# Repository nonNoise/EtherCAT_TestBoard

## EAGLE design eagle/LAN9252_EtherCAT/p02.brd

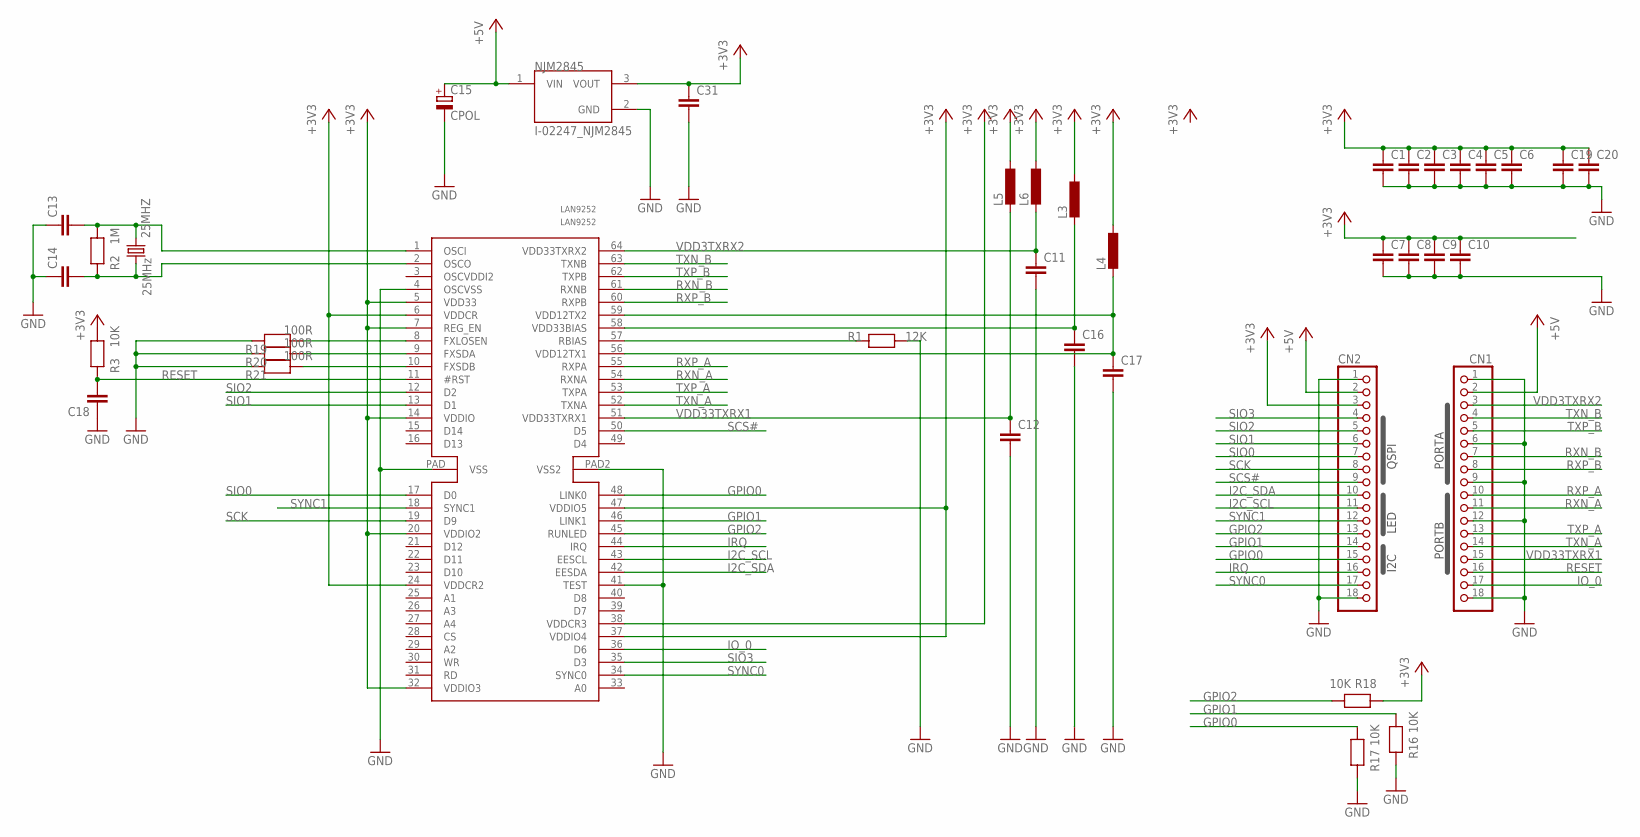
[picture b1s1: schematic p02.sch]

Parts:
25MHZ: 25MHz; HC49/S
C1, C2, C3, C4, C5, C6, C7, C8, C9, C10, C11, C12, C13, C14, C16, C17, C18, C31: C_1068; C0603
C15: CPOL; 153CLV-0605
C19, C20: C_2012; C0805K
CN1, CN2: PINHD-1X18; 1X18
L3, L4, L5, L6: L-EUL2012C; L2012C
LAN9252: LAN9252; QFN-64_02
NJM2845: I-02247_NJM2845; TO252
R1: 12K; R0603
R2: 1M; R0603
R3, R16, R17, R18: 10K; R0603
R19, R20, R21: 100R; R0603

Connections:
+3V3: C1.1, C2.1, C3.1, C4.1, C5.1, C6.1, C7.1, C8.1, C9.1, C10.1, C19.1, C20.1, C31.1, CN2.3, L3.1, L4.1, L5.1, L6.1, LAN9252.5 (VDD33), LAN9252.6 (VDDCR), LAN9252.7 (REG_EN), LAN9252.14 (VDDIO), LAN9252.20 (VDDIO2), LAN9252.24 (VDDCR2), LAN9252.32 (VDDIO3), LAN9252.37 (VDDIO4), LAN9252.38 (VDDCR3), LAN9252.47 (VDDIO5), NJM2845.3 (VOUT), R3.2, R18.1
+5V: C15.+, CN1.2, CN2.2, NJM2845.1 (VIN)
GND: C1.2, C2.2, C3.2, C4.2, C5.2, C6.2, C7.2, C8.2, C9.2, C10.2, C11.2, C12.2, C13.1, C14.1, C15.-, C16.2, C17.2, C18.1, C19.2, C20.2, C31.2, CN1.1, CN1.6, CN1.9, CN1.12, CN1.18, CN2.1, CN2.18, LAN9252.4 (OSCVSS), LAN9252.41 (TEST), LAN9252.PAD (VSS), LAN9252.PAD2 (VSS2), NJM2845.2 (GND), R1.1, R16.1, R17.1, R19.1, R20.1, R21.1
GPIO0: CN2.15, LAN9252.48 (LINK0), R17.2
GPIO1: CN2.14, LAN9252.46 (LINK1), R16.2
GPIO2: CN2.13, LAN9252.45 (RUNLED), R18.2
I2C_SCL: CN2.11, LAN9252.43 (EESCL)
I2C_SDA: CN2.10, LAN9252.42 (EESDA)
IO_0: CN1.17, LAN9252.36 (D6)
IRQ: CN2.16, LAN9252.44 (IRQ)
unnamed: LAN9252.57 (RBIAS), R1.2
unnamed: LAN9252.8 (FXLOSEN), R19.2
unnamed: LAN9252.9 (FXSDA), R20.2
unnamed: 25MHZ.2, C13.2, LAN9252.1 (OSCI), R2.2
unnamed: C17.1, L4.2, LAN9252.56 (VDD12TX1), LAN9252.59 (VDD12TX2)
unnamed: 25MHZ.1, C14.2, LAN9252.2 (OSCO), R2.1
unnamed: LAN9252.10 (FXSDB), R21.2
unnamed: C16.1, L3.2, LAN9252.58 (VDD33BIAS)
RESET: C18.2, CN1.16, LAN9252.11 (#RST), R3.1
RXN_A: CN1.11, LAN9252.54 (RXNA)
RXN_B: CN1.7, LAN9252.61 (RXNB)
RXP_A: CN1.10, LAN9252.55 (RXPA)
RXP_B: CN1.8, LAN9252.60 (RXPB)
SCK: CN2.8, LAN9252.19 (D9)
SCS#: CN2.9, LAN9252.50 (D5)
SIO0: CN2.7, LAN9252.17 (D0)
SIO1: CN2.6, LAN9252.13 (D1)
SIO2: CN2.5, LAN9252.12 (D2)
SIO3: CN2.4, LAN9252.35 (D3)
SYNC0: CN2.17, LAN9252.34 (SYNC0)
SYNC1: CN2.12, LAN9252.18 (SYNC1)
TXN_A: CN1.14, LAN9252.52 (TXNA)
TXN_B: CN1.4, LAN9252.63 (TXNB)
TXP_A: CN1.13, LAN9252.53 (TXPA)
TXP_B: CN1.5, LAN9252.62 (TXPB)
VDD3TXRX2: C11.1, CN1.3, L6.2, LAN9252.64 (VDD33TXRX2)
VDD33TXRX1: C12.1, CN1.15, L5.2, LAN9252.51 (VDD33TXRX1)

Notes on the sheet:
PORTA
PORTB
QSPI
LED
I2C

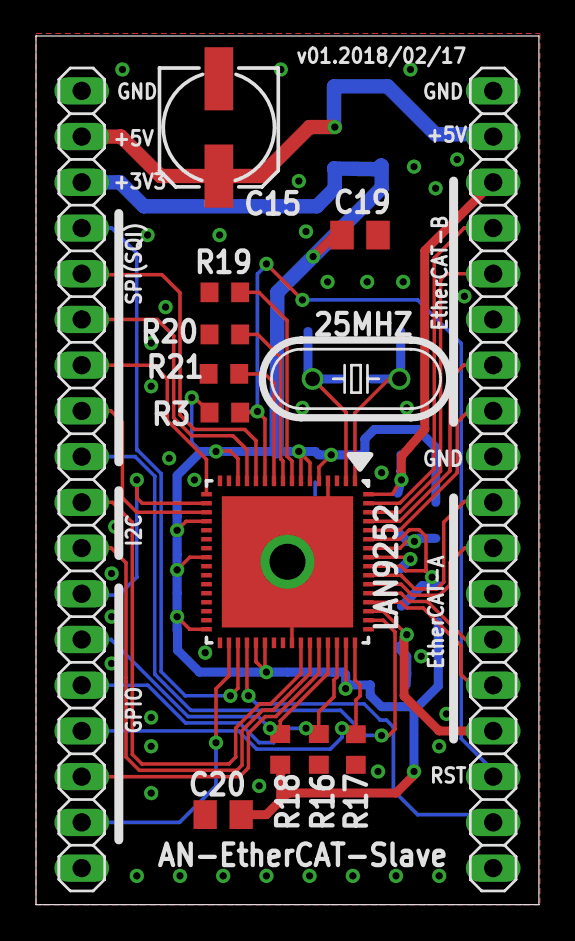
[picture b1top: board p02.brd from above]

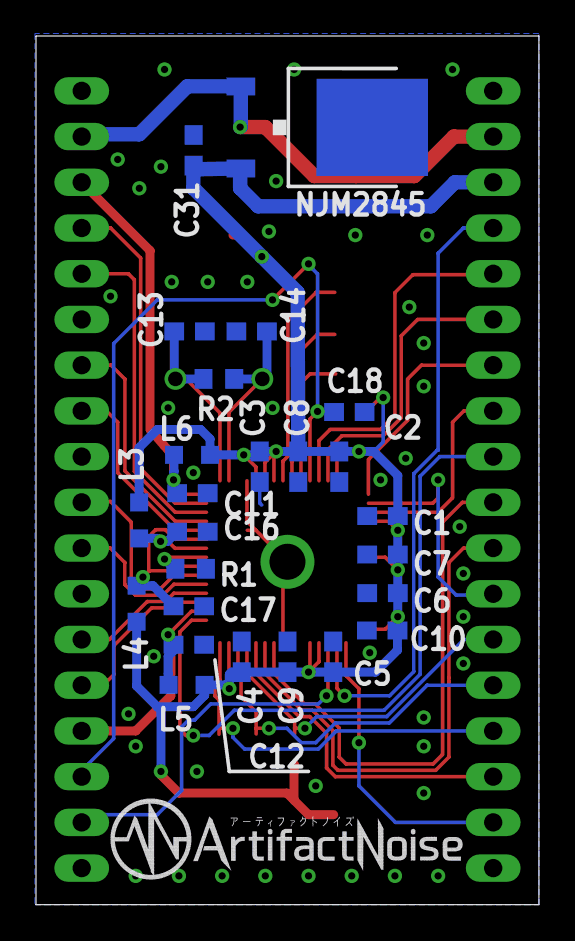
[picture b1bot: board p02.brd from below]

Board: 2 copper layers, 27.9 x 48.3 mm, 40 parts (26 on the bottom side), 37 nets.

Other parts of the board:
U$1: AN-LOGO2

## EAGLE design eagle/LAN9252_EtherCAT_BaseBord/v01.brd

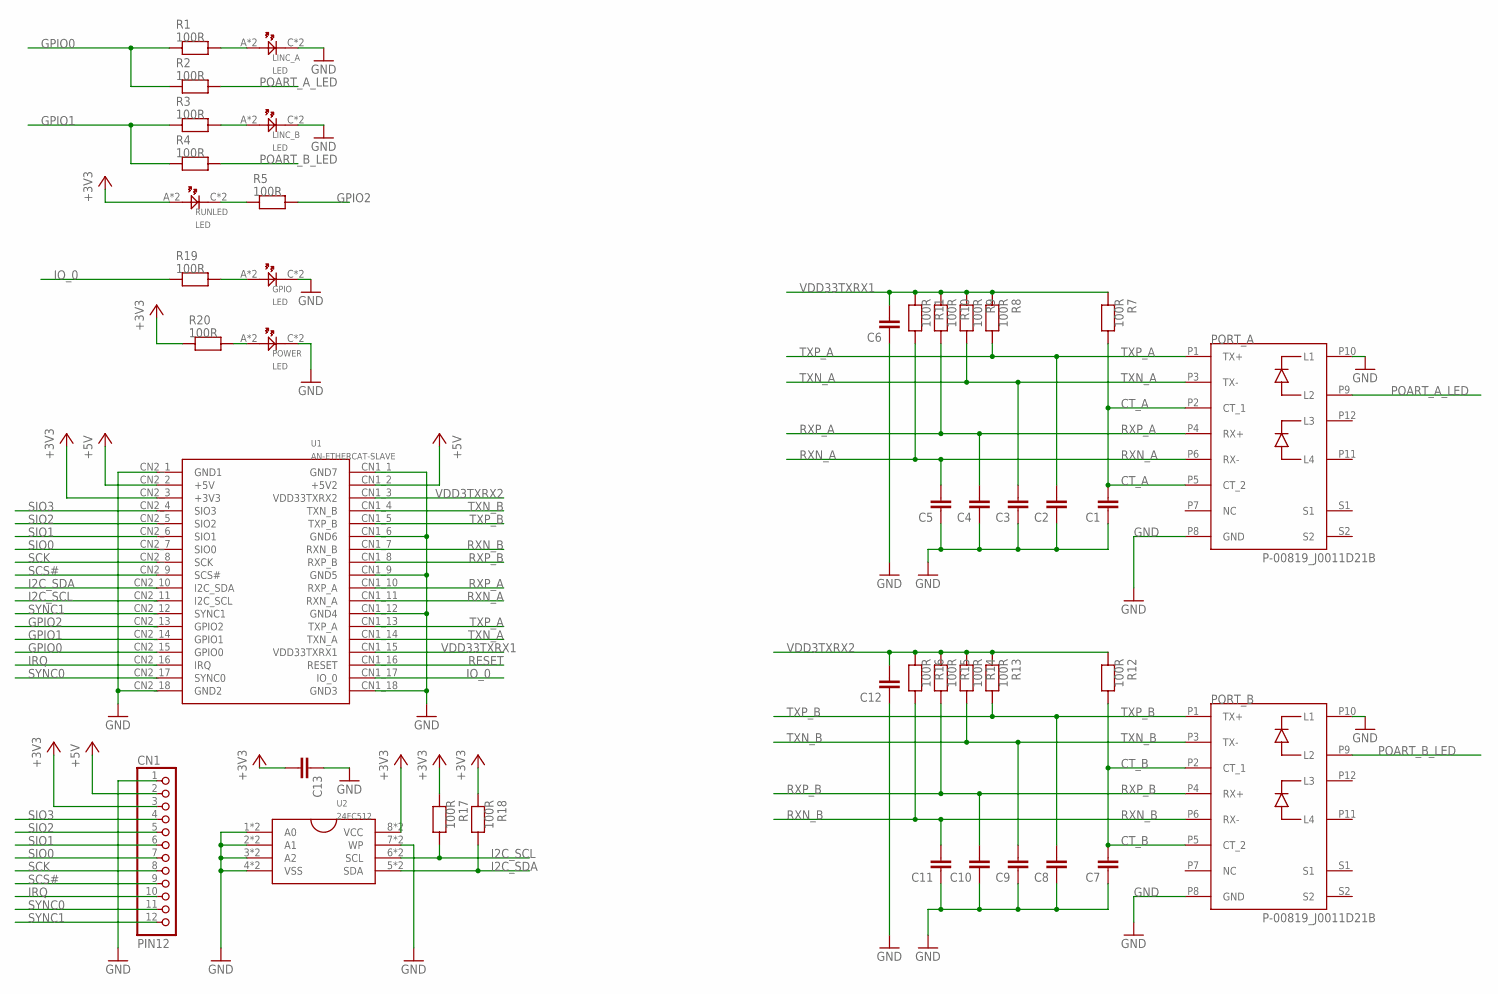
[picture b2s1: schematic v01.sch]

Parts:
C1, C2, C3, C4, C5, C6, C7, C8, C9, C10, C11, C12, C13: C_1068; C0603
CN1: PIN12
GPIO: LED; CHIPLED_0805
LINC_A: LED; CHIPLED_0805
LINC_B: LED; CHIPLED_0805
PORT_A: P-00819_J0011D21B; J0011D21B
PORT_B: P-00819_J0011D21B; J0011D21B
POWER: LED; CHIPLED_0805
R1, R2, R3, R4, R5, R7, R8, R9, R10, R11, R12, R13, R14, R15, R16, R17, R18, R19, R20: 100R; R0603
RUNLED: LED; CHIPLED_0805
U1: AN-ETHERCAT-SLAVE
U2: 24FC512; SOP8

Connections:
+3V3: C13.2, CN1.3, R17.1, R18.1, R20.1, RUNLED.A, RUNLED.DA (A), U1.CN2_3 (+3V3), U2.8 (VCC), U2.D8 (VCC)
+5V: CN1.2, U1.CN1_2 (+5V2), U1.CN2_2 (+5V)
CT_A: C1.2, PORT_A.P2 (CT_1), PORT_A.P5 (CT_2), R7.2
CT_B: C7.2, PORT_B.P2 (CT_1), PORT_B.P5 (CT_2), R12.2
GND: C1.1, C2.1, C3.1, C4.1, C5.1, C6.1, C7.1, C8.1, C9.1, C10.1, C11.1, C12.1, C13.1, CN1.1, GPIO.C, GPIO.DC (C), LINC_A.C, LINC_A.DC (C), LINC_B.C, LINC_B.DC (C), PORT_A.P8 (GND), PORT_A.P10 (L1), PORT_B.P8 (GND), PORT_B.P10 (L1), POWER.C, POWER.DC (C), U1.CN1_1 (GND7), U1.CN1_6 (GND6), U1.CN1_9 (GND5), U1.CN1_12 (GND4), U1.CN1_18 (GND3), U1.CN2_1 (GND1), U1.CN2_18 (GND2), U2.1 (A0), U2.2 (A1), U2.3 (A2), U2.4 (VSS), U2.7 (WP), U2.D1 (A0), U2.D2 (A1), U2.D3 (A2), U2.D4 (VSS), U2.D7 (WP)
GPIO0: R1.1, R2.1, U1.CN2_15 (GPIO0)
GPIO1: R3.1, R4.1, U1.CN2_14 (GPIO1)
GPIO2: R5.2, U1.CN2_13 (GPIO2)
I2C_SCL: R17.2, U1.CN2_11 (I2C_SCL), U2.6 (SCL), U2.D6 (SCL)
I2C_SDA: R18.2, U1.CN2_10 (I2C_SDA), U2.5 (SDA), U2.D5 (SDA)
IO_0: R19.1, U1.CN1_17 (IO_0)
IRQ: CN1.10, U1.CN2_16 (IRQ)
unnamed: LINC_A.A, LINC_A.DA (A), R1.2
unnamed: LINC_B.A, LINC_B.DA (A), R3.2
unnamed: R5.1, RUNLED.C, RUNLED.DC (C)
unnamed: GPIO.A, GPIO.DA (A), R19.2
unnamed: POWER.A, POWER.DA (A), R20.2
POART_A_LED: PORT_A.P9 (L2), R2.2
POART_B_LED: PORT_B.P9 (L2), R4.2
RESET: U1.CN1_16 (RESET)
RXN_A: C5.2, PORT_A.P6 (RX-), R11.2, U1.CN1_11 (RXN_A)
RXN_B: C11.2, PORT_B.P6 (RX-), R16.2, U1.CN1_7 (RXN_B)
RXP_A: C4.2, PORT_A.P4 (RX+), R10.2, U1.CN1_10 (RXP_A)
RXP_B: C10.2, PORT_B.P4 (RX+), R15.2, U1.CN1_8 (RXP_B)
SCK: CN1.8, U1.CN2_8 (SCK)
SCS#: CN1.9, U1.CN2_9 (SCS#)
SIO0: CN1.7, U1.CN2_7 (SIO0)
SIO1: CN1.6, U1.CN2_6 (SIO1)
SIO2: CN1.5, U1.CN2_5 (SIO2)
SIO3: CN1.4, U1.CN2_4 (SIO3)
SYNC0: CN1.11, U1.CN2_17 (SYNC0)
SYNC1: CN1.12, U1.CN2_12 (SYNC1)
TXN_A: C3.2, PORT_A.P3 (TX-), R9.2, U1.CN1_14 (TXN_A)
TXN_B: C9.2, PORT_B.P3 (TX-), R14.2, U1.CN1_4 (TXN_B)
TXP_A: C2.2, PORT_A.P1 (TX+), R8.2, U1.CN1_13 (TXP_A)
TXP_B: C8.2, PORT_B.P1 (TX+), R13.2, U1.CN1_5 (TXP_B)
VDD3TXRX2: C12.2, R12.1, R13.1, R14.1, R15.1, R16.1, U1.CN1_3 (VDD33TXRX2)
VDD33TXRX1: C6.2, R7.1, R8.1, R9.1, R10.1, R11.1, U1.CN1_15 (VDD33TXRX1)

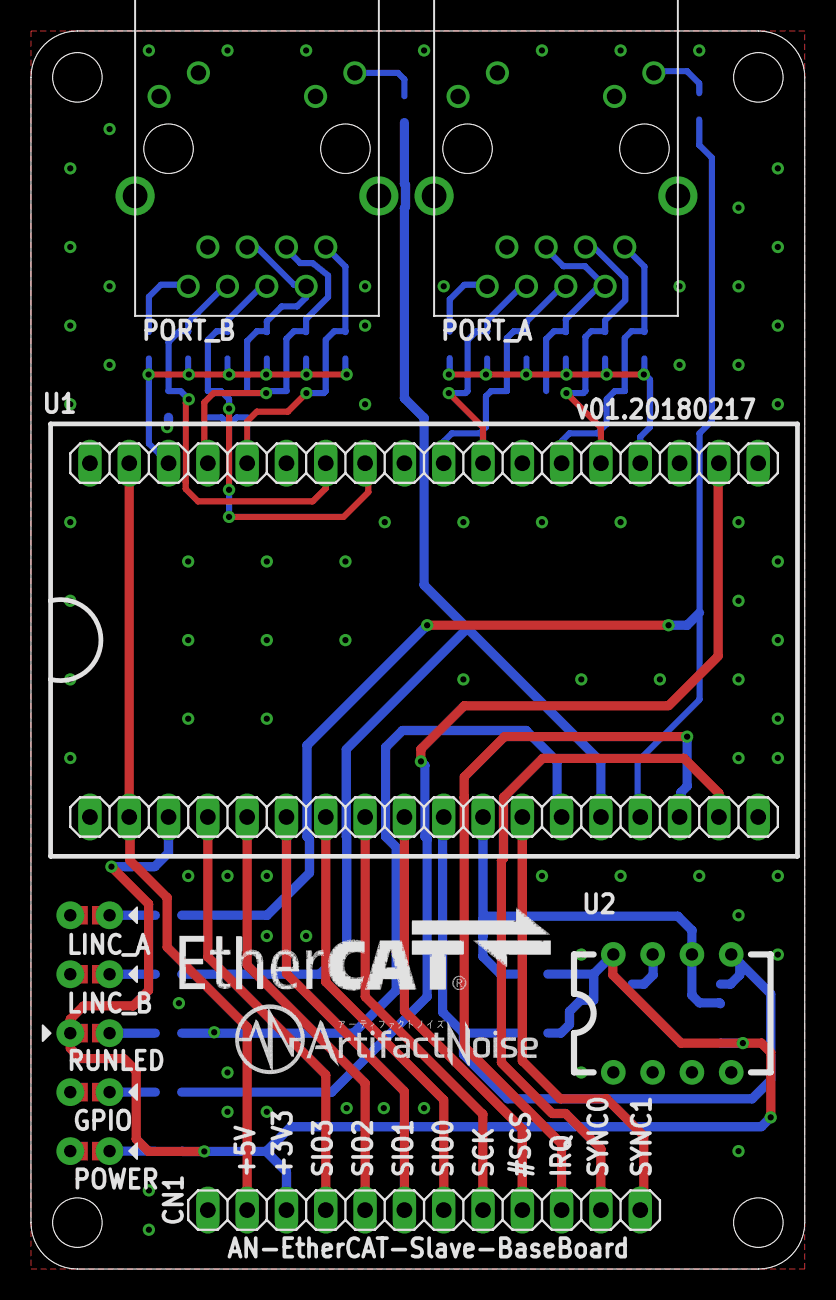
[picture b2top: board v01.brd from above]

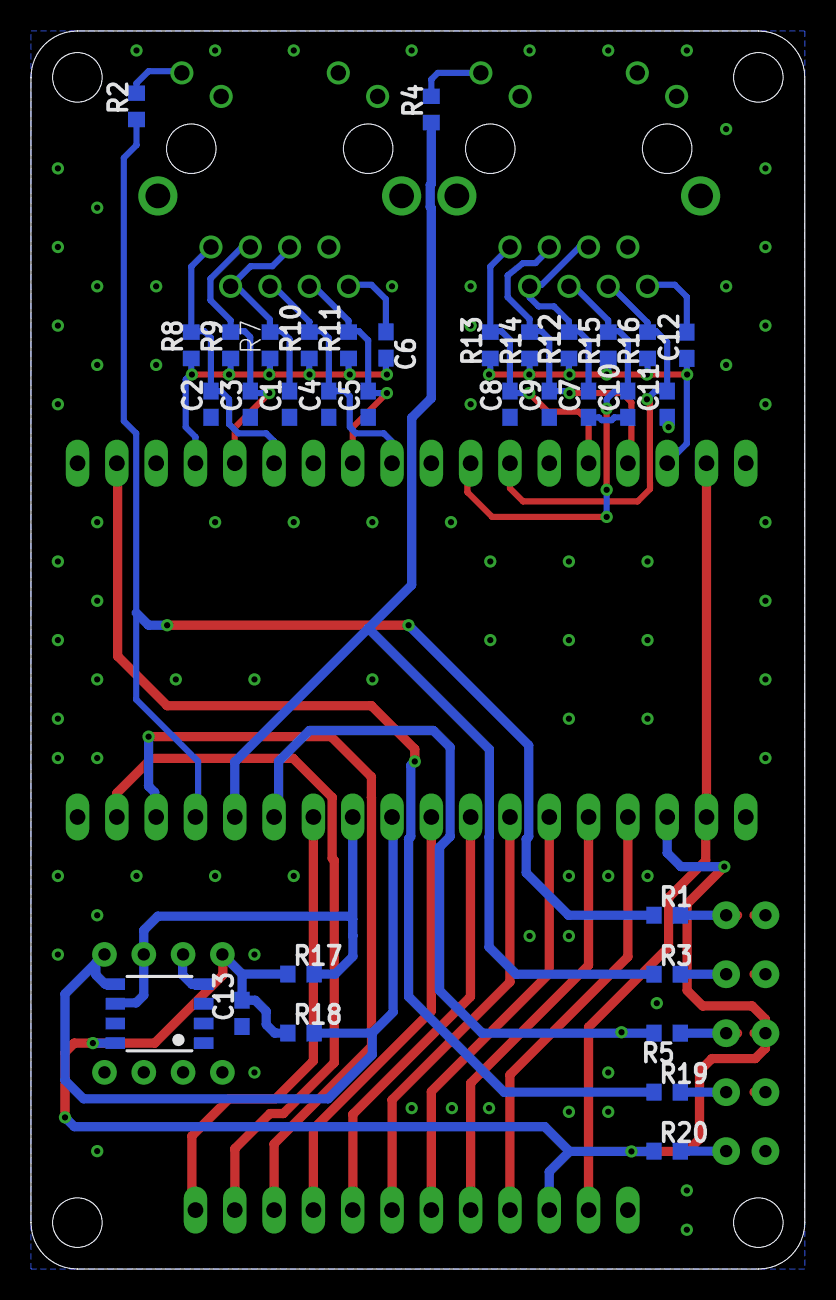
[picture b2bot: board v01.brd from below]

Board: 2 copper layers, 50.0 x 80.0 mm, 44 parts (32 on the bottom side), 37 nets.

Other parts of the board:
U$1: ETHERCAT_LOGO
U$2: AN-LOGO2

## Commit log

2018-02-20 new add
